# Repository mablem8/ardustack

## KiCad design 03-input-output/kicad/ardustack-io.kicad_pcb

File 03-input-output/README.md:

# Ardustack Input/Output Board

The I/O PCB for a through-hole Arduino stack

## Directory Contents

* **3d-models**: Contains component `.stp` files for import
* **components**: Contains component `.lib` files for import
* **datasheets**: Contains component datasheets
* **footprints**: Contains component `.kicad_mod` files for import
* **gerbers**: Contains the most recent set of Gerber files
* **kicad**: Contains the KiCad project files
* **versions**: Contains `.zip` files of Gerber files submitted for fabrication
* [BOM.csv](BOM.csv): Bill of materials
* [LICENSE](LICENSE): License
* [NOTES.md](NOTES.md): Useful notes if setting up a KiCad project from scratch
* [README.md](README.md): This document

## License

Written by Bradley Denby  
Other contributors: None

See the [LICENSE](LICENSE) file for the license.

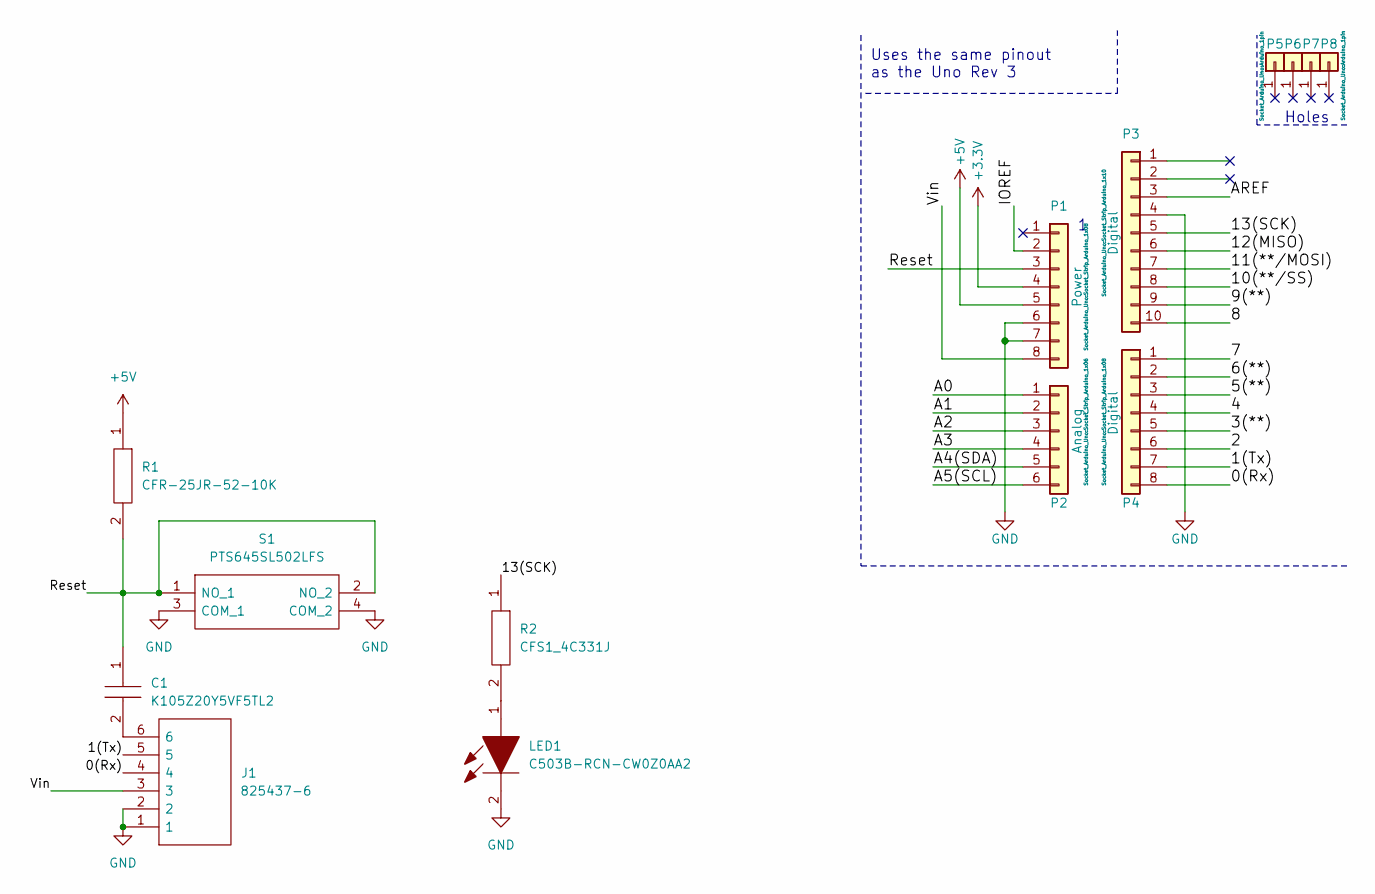
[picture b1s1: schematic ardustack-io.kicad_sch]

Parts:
C1: K105Z20Y5VF5TL2; Manufacturer_Part_Number K105Z20Y5VF5TL2; Mouser Part Number 594-K105Z20Y5VF5TL2
J1: 825437-6; Manufacturer_Part_Number 825437-6; Mouser Part Number 571-825437-6
LED1: C503B-RCN-CW0Z0AA2; C503BRCNCW0Z0AA2; Manufacturer_Part_Number C503B-RCN-CW0Z0AA2; Mouser Part Number 941-C503BRCNCW0Z0AA2
P1: Power; Socket_Strip_Arduino_1x08
P2: Analog; Socket_Strip_Arduino_1x06
P3: Digital; Socket_Strip_Arduino_1x10
P4: Digital; Socket_Strip_Arduino_1x08
P5, P6, P7, P8: CONN_01X01; Arduino_1pin
R1: CFR-25JR-52-10K; RESAD1590W60L630D240; Manufacturer_Part_Number CFR-25JR-52-10K; Mouser Part Number 603-CFR-25JR-5210K
R2: CFS1_4C331J; RESAD1020W45L320D175; Manufacturer_Part_Number CFS1/4C331J; Mouser Part Number 660-CFS1/4C331J
S1: PTS645SL502LFS; Manufacturer_Part_Number PTS645SL502LFS; Mouser Part Number 611-PTS645SL502

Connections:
+3V3: P1.4
+5V: P1.5, R1.1
/0(Rx): J1.4, P4.8
/1(Tx): J1.5, P4.7
/2: P4.6
/3(**): P4.5
/4: P4.4
/5(**): P4.3
/6(**): P4.2
/7: P4.1
/8: P3.10
/9(**): P3.9
/10(**/SS): P3.8
/11(**/MOSI): P3.7
/12(MISO): P3.6
/13(SCK): P3.5, R2.1
/A0: P2.1
/A1: P2.2
/A2: P2.3
/A3: P2.4
/A4(SDA): P2.5
/A5(SCL): P2.6
/AREF: P3.3
/IOREF: P1.2
/Reset: C1.1, P1.3, R1.2, S1.1 (NO_1), S1.2 (NO_2)
/Vin: J1.3, P1.8
GND: J1.1, J1.2, LED1.2, P1.6, P1.7, P3.4, S1.3 (COM_1), S1.4 (COM_2)
unnamed: C1.2, J1.6
unnamed: LED1.1, R2.2

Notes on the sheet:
Holes
Uses the same pinout as the Uno Rev 3

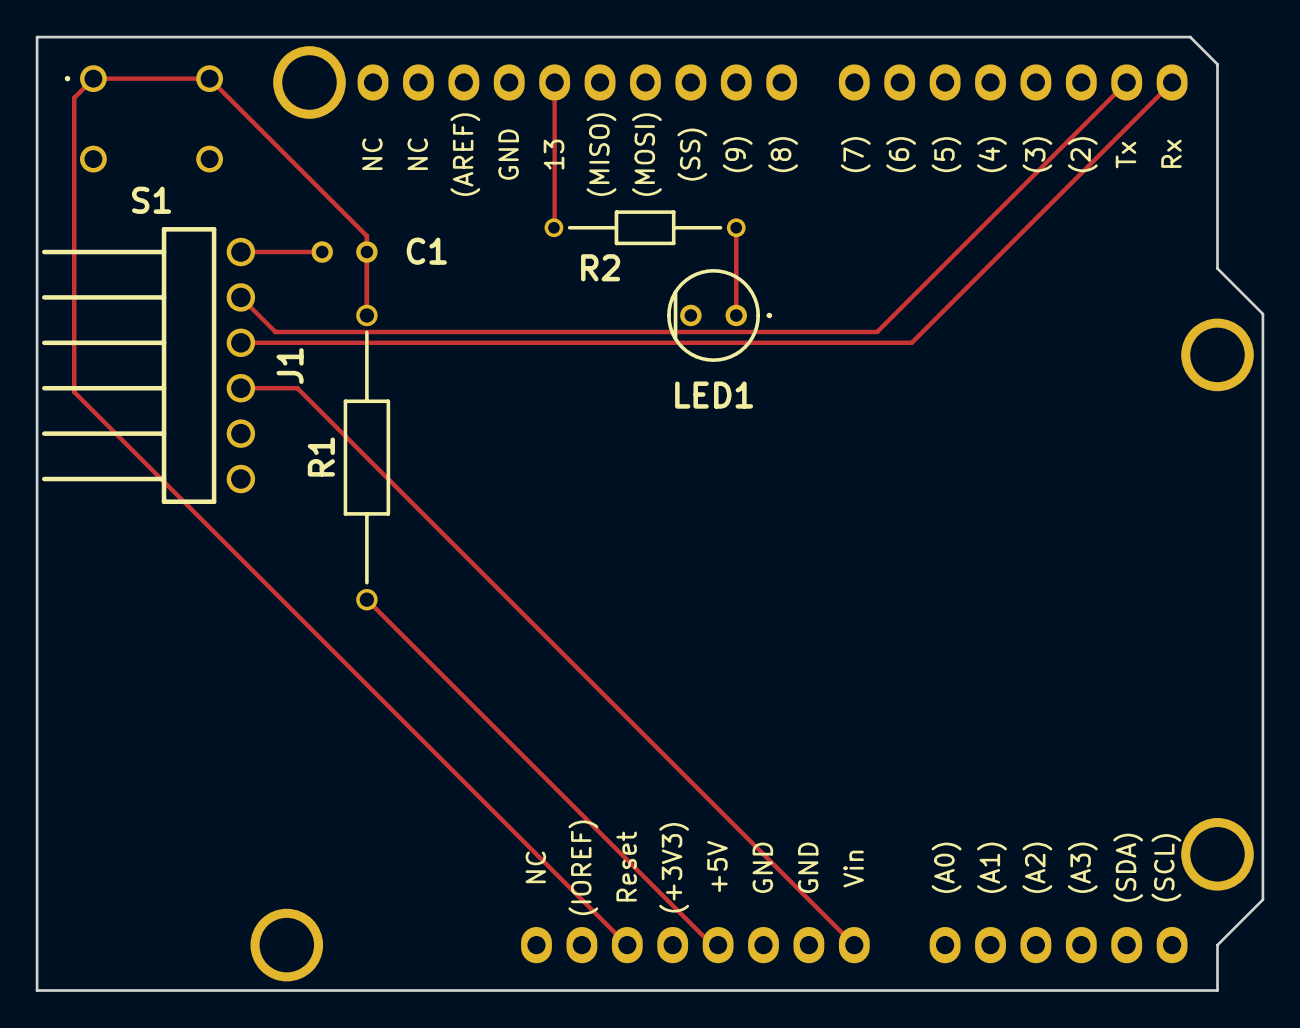
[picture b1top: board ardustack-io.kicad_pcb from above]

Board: 2 copper layers, 68.6 x 53.3 mm, 14 parts (0 on the bottom side), 9 nets.

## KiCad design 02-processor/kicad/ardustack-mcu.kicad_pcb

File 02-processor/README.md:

# Ardustack Processor Board

The microcontroller PCB for a through-hole Arduino stack

## Directory Contents

* **3d-models**: Contains component `.stp` files for import
* **components**: Contains component `.lib` files for import
* **datasheets**: Contains component datasheets
* **footprints**: Contains component `.kicad_mod` files for import
* **gerbers**: Contains the most recent set of Gerber files
* **kicad**: Contains the KiCad project files
* **versions**: Contains `.zip` files of Gerber files submitted for fabrication
* [BOM.csv](BOM.csv): Bill of materials
* [LICENSE](LICENSE): License
* [NOTES.md](NOTES.md): Useful notes if setting up a KiCad project from scratch
* [README.md](README.md): This document

## License

Written by Bradley Denby  
Other contributors: None

See the [LICENSE](LICENSE) file for the license.

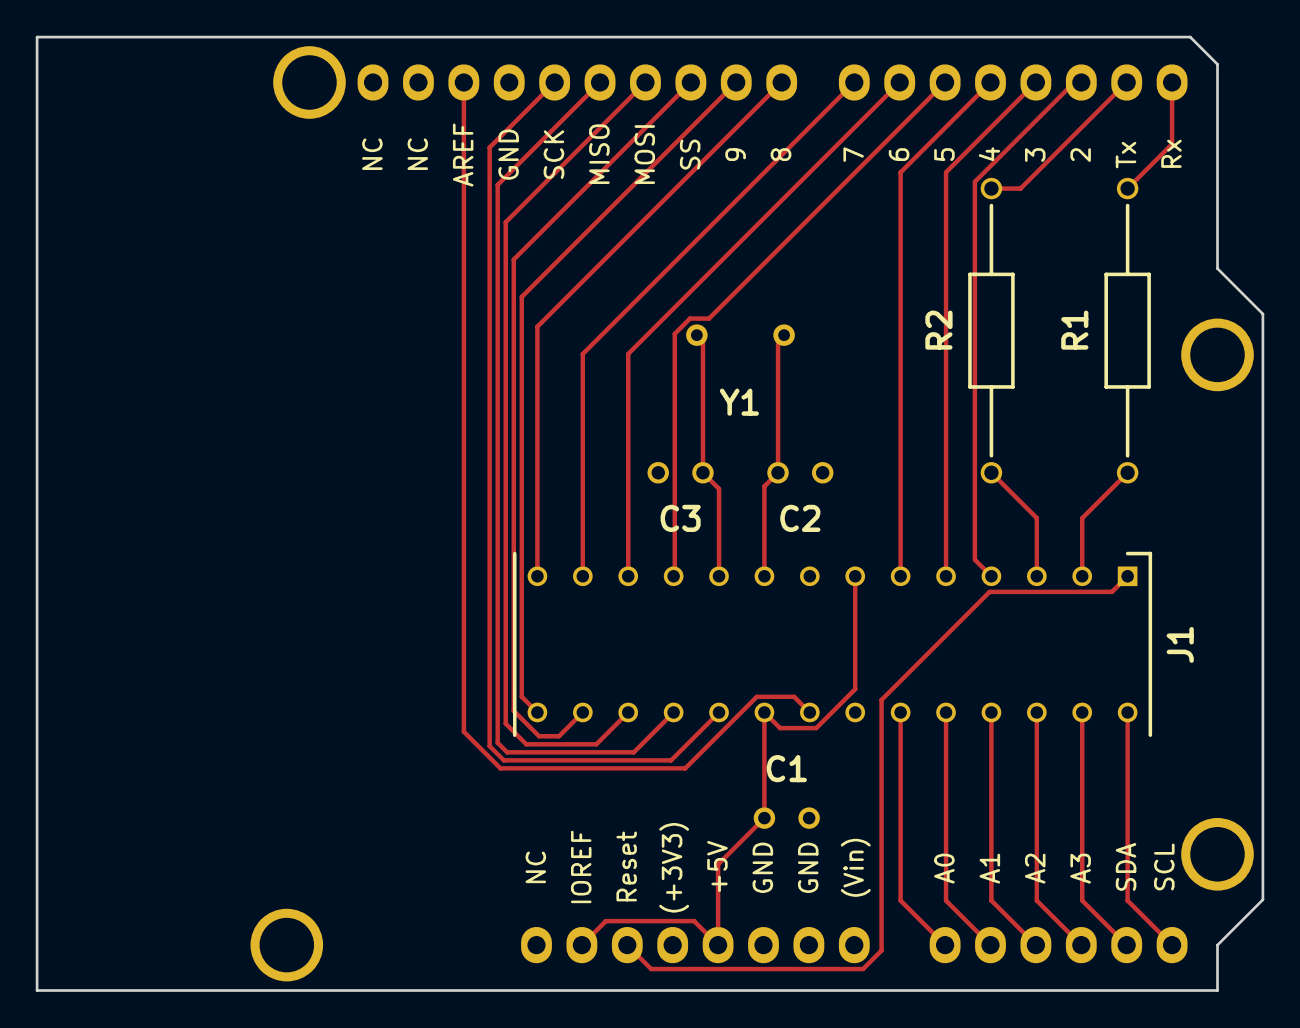
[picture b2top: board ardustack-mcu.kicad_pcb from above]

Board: 2 copper layers, 68.6 x 53.3 mm, 15 parts (0 on the bottom side), 28 nets.

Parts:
C1: K105Z20Y5VF5TL2
C2, C3: K220J15C0GF5TL2
J1: 1-2199298-9; DIPS1524W51P254L3556H457Q28N
P1: Power; Socket_Strip_Arduino_1x08
P2: Analog; Socket_Strip_Arduino_1x06
P3: Digital; Socket_Strip_Arduino_1x10
P4: Digital; Socket_Strip_Arduino_1x08
P5, P6, P7, P8: CONN_01X01; Arduino_1pin
R1, R2: CFR-25JR-52-10K; RESAD1590W60L630D240
Y1: ABL-16.000MHZ-B2; ABL16000MHZB2

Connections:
+5V: C1.1, J1.7, J1.20, P1.2, P1.5
/0(Rx): P4.8, R1.2
/1(Tx): P4.7, R2.2
/2: J1.4, P4.6
/3(**): J1.5, P4.5
/4: J1.6, P4.4
/5(**): J1.11, P4.3
/6(**): J1.12, P4.2
/7: J1.13, P4.1
/8: J1.14, P3.10
/9(**): J1.15, P3.9
/10(**/SS): J1.16, P3.8
/11(**/MOSI): J1.17, P3.7
/12(MISO): J1.18, P3.6
/13(SCK): J1.19, P3.5
/A0: J1.23, P2.1
/A1: J1.24, P2.2
/A2: J1.25, P2.3
/A3: J1.26, P2.4
/A4(SDA): J1.27, P2.5
/A5(SCL): J1.28, P2.6
/AREF: J1.21, P3.3
/CLK1: C2.1, J1.9, Y1.1 (X1)
/CLK2: C3.1, J1.10, Y1.2 (X2)
/Reset: J1.1, P1.3
GND: C1.2, C2.2, C3.2, J1.8, J1.22, P1.6, P1.7, P3.4
unnamed: J1.2, R1.1
unnamed: J1.3, R2.1

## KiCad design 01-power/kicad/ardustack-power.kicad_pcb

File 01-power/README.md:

# Ardustack Power Board

The power management PCB for a through-hole Arduino stack

## Directory Contents

* **3d-models**: Contains component `.stp` files for import
* **components**: Contains component `.lib` files for import
* **datasheets**: Contains component datasheets
* **footprints**: Contains component `.kicad_mod` files for import
* **gerbers**: Contains the most recent set of Gerber files
* **kicad**: Contains the KiCad project files
* **versions**: Contains `.zip` files of Gerber files submitted for fabrication
* [BOM.csv](BOM.csv): Bill of materials
* [LICENSE](LICENSE): License
* [NOTES.md](NOTES.md): Useful notes if setting up a KiCad project from scratch
* [README.md](README.md): This document

## License

Written by Bradley Denby  
Other contributors: None

See the [LICENSE](LICENSE) file for the license.

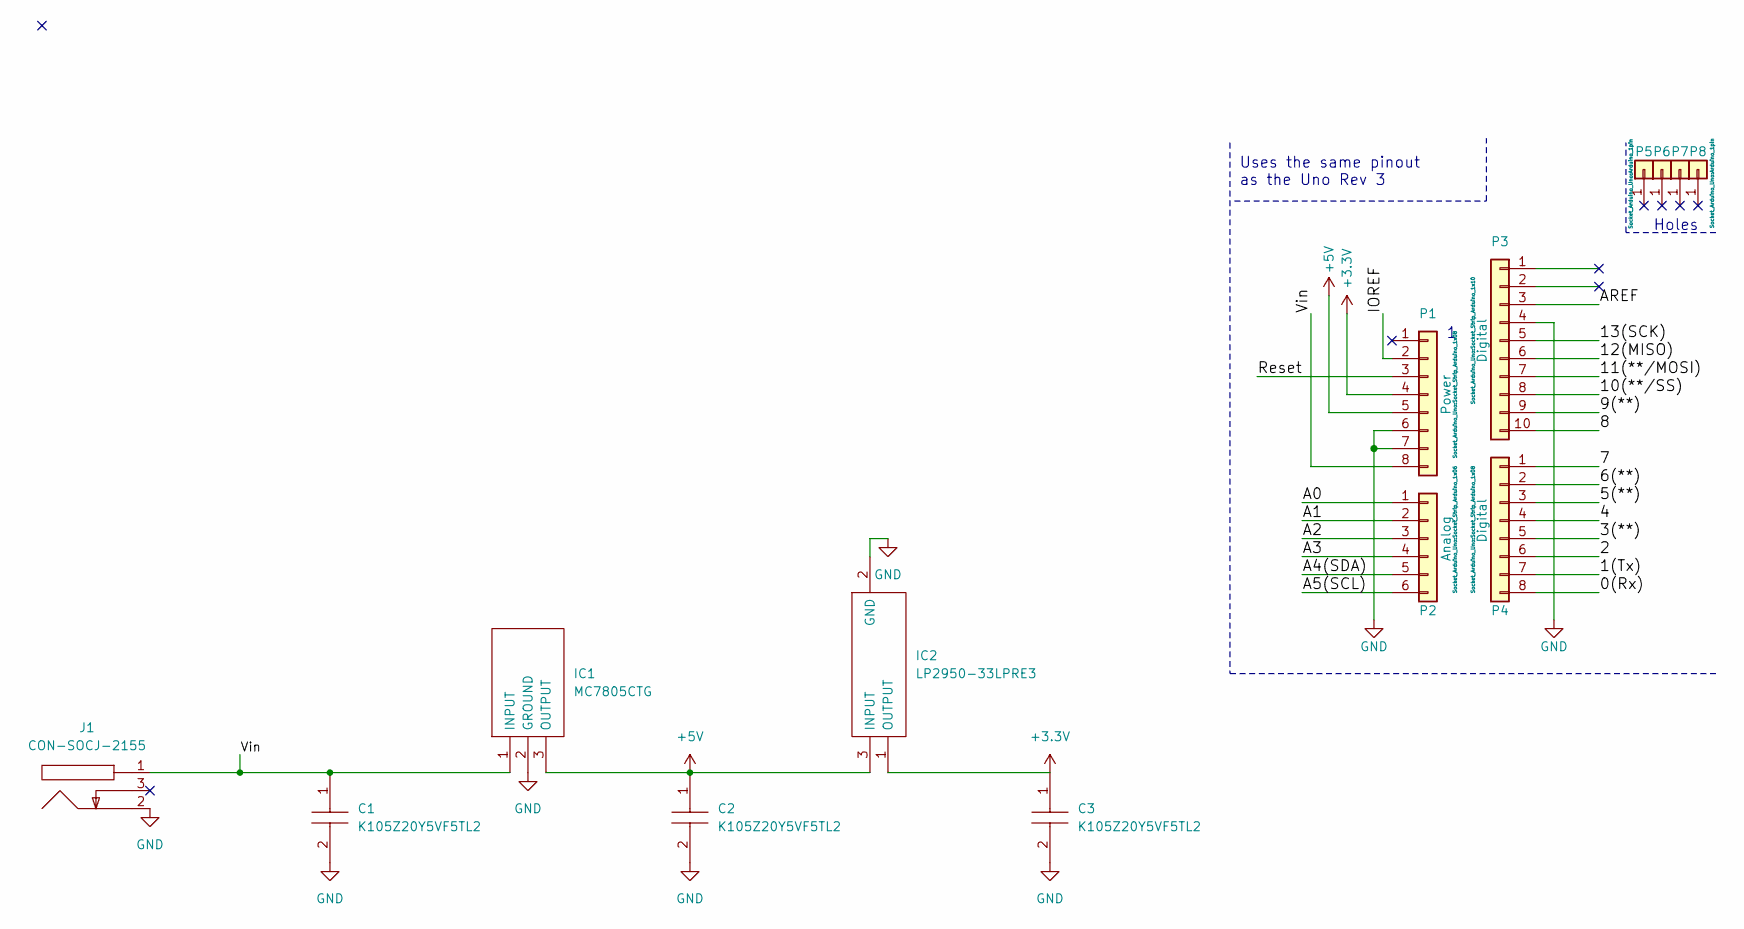
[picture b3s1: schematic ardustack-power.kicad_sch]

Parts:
C1, C2, C3: K105Z20Y5VF5TL2; Manufacturer_Part_Number K105Z20Y5VF5TL2; Mouser Part Number 594-K105Z20Y5VF5TL2
IC1: MC7805CTG; TO254P482X997X2018-3P; Manufacturer_Part_Number MC7805CTG; Mouser Part Number 863-MC7805CTG
IC2: LP2950-33LPRE3; TL431CLP; Manufacturer_Part_Number LP2950-33LPRE3; Mouser Part Number 595-LP2950-33LPRE3
J1: CON-SOCJ-2155; CONSOCJ2155; Manufacturer_Part_Number CON-SOCJ-2155; Mouser Part Number 992-CON-SOCJ-2155
P1: Power; Socket_Strip_Arduino_1x08
P2: Analog; Socket_Strip_Arduino_1x06
P3: Digital; Socket_Strip_Arduino_1x10
P4: Digital; Socket_Strip_Arduino_1x08
P5, P6, P7, P8: CONN_01X01; Arduino_1pin

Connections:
+3V3: C3.1, IC2.1 (OUTPUT), P1.4
+5V: C2.1, IC1.3 (OUTPUT), IC2.3 (INPUT), P1.5
/0(Rx): P4.8
/1(Tx): P4.7
/2: P4.6
/3(**): P4.5
/4: P4.4
/5(**): P4.3
/6(**): P4.2
/7: P4.1
/8: P3.10
/9(**): P3.9
/10(**/SS): P3.8
/11(**/MOSI): P3.7
/12(MISO): P3.6
/13(SCK): P3.5
/A0: P2.1
/A1: P2.2
/A2: P2.3
/A3: P2.4
/A4(SDA): P2.5
/A5(SCL): P2.6
/AREF: P3.3
/IOREF: P1.2
/Reset: P1.3
/Vin: C1.1, IC1.1 (INPUT), J1.1, P1.8
GND: C1.2, C2.2, C3.2, IC1.2 (GROUND), IC2.2 (GND), J1.2, P1.6, P1.7, P3.4

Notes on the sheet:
Holes
Uses the same pinout as the Uno Rev 3

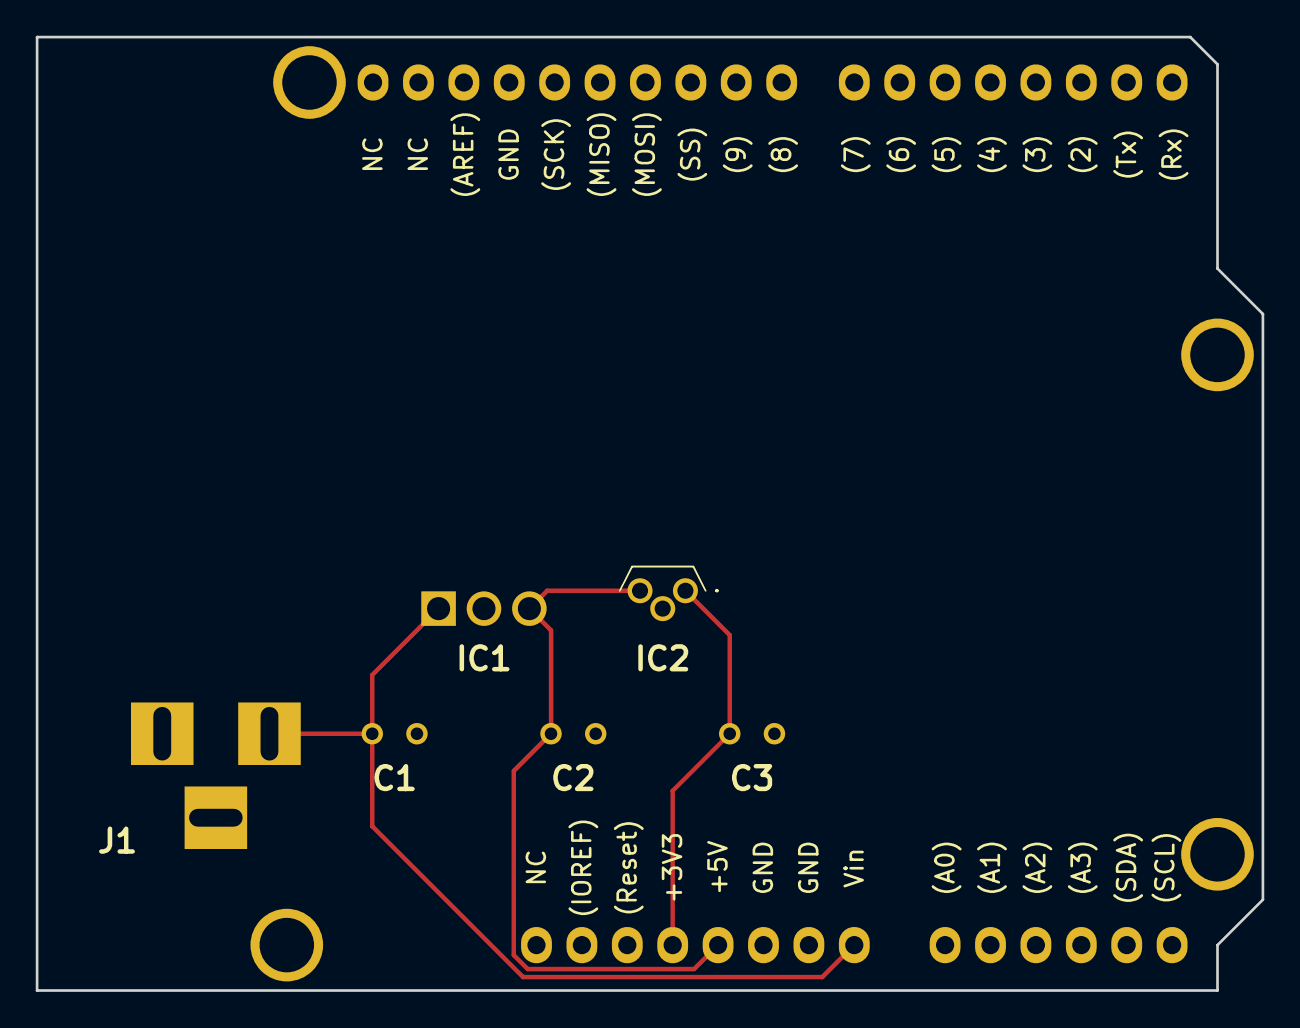
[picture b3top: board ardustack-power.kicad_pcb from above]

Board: 2 copper layers, 68.6 x 53.3 mm, 14 parts (0 on the bottom side), 4 nets.

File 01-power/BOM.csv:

label,count,id,mouser,url,description
IC1,1,MC7805CTG,863-MC7805CTG,https://componentsearchengine.com/part-view/MC7805CTG/ON%20S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,Linear voltage regulator; Through hole TO-220-3; 1 Output; Positive; 5V; 1A; Fixed; 7-35V in; 25mV load reg.; 20mV line reg.; 0 - +125 C
IC2,1,LP2950-33LPRE3,595-LP2950-33LPRE3,https://componentsearchengine.com/part-view/LP2950-33LPRE3/T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,LDO voltage regulator; Through hole TO-92-3; 1 Output; Positive; 3.3V; 100mA; Fixed; 2-30V in; 110mV dropout; 75uA quiescent; -40 - +125 C
J1,1,CON-SOCJ-2155,992-CON-SOCJ-2155,https://componentsearchengine.com/part-view/CON-SOCJ-2155/Gravitech,DC power connector; 2.1mm inside diameter; 5.5mm outside diameter; solder lug; right angle; DC power jack
C1; C2; C3,3,K105Z20Y5VF5TL2,594-K105Z20Y5VF5TL2,https://componentsearchengine.com/part-view/K105Z20Y5VF5TL2/Vishay,1 uF; radial termination; 50V rating; -20% +80% tolerance; -30 - +85 C

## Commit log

2021-12-31 Initial commit of Ardustack power board files
2022-01-02 Initial commit of Ardustack microcontroller board files
2022-01-02 Initial commit of Ardustack I/O board files
2022-01-02 Updates Ardustack power board PCB silkscreen
2022-01-02 Updates Ardustack microcontroller board PCB silkscreen
2022-01-02 Updates Ardustack I/O board PCB silkscreen
2022-01-03 Adds v0.9.0 Gerber ZIP files
2022-01-03 Updates PCBs with name and version
2022-01-13 Updates power, processor, and I/O boards to v1.0.0
2022-01-21 Adds software instructions
2022-02-06 Adds robot software
2022-02-06 Updates robot software
